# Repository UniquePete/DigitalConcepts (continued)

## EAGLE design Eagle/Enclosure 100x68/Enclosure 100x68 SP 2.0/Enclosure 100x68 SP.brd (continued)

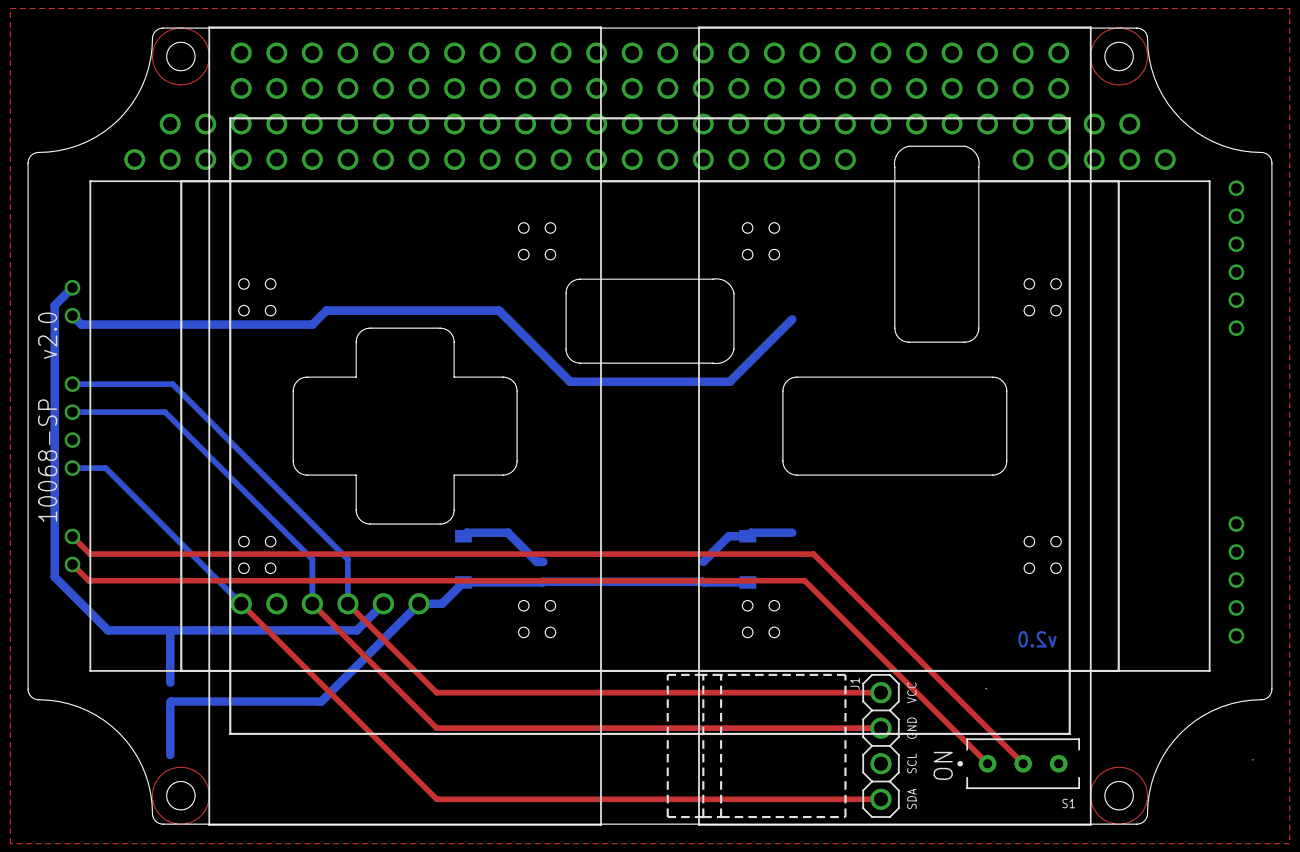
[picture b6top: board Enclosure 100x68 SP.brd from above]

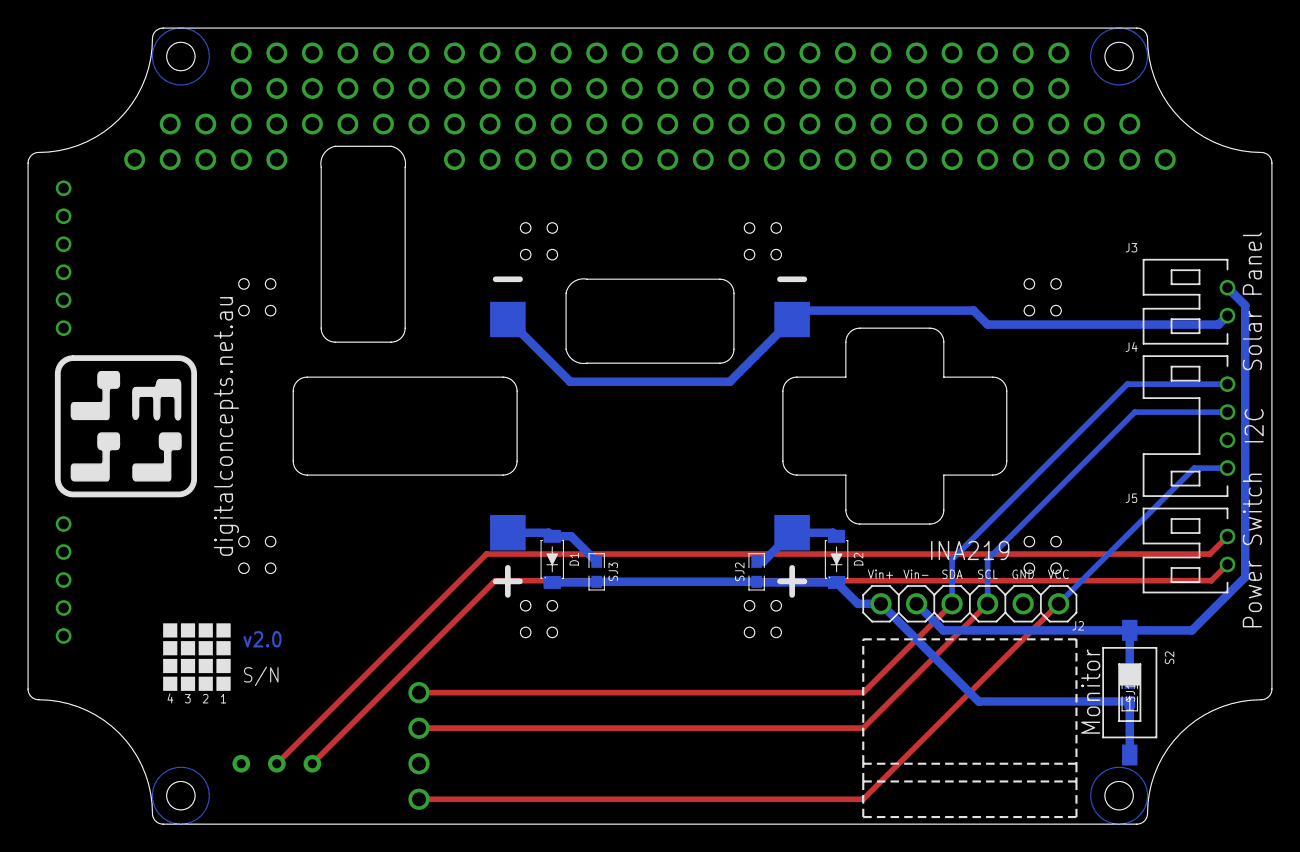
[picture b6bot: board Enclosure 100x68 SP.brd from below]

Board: 2 copper layers, 88.9 x 56.9 mm, 17 parts (14 on the bottom side), 11 nets.

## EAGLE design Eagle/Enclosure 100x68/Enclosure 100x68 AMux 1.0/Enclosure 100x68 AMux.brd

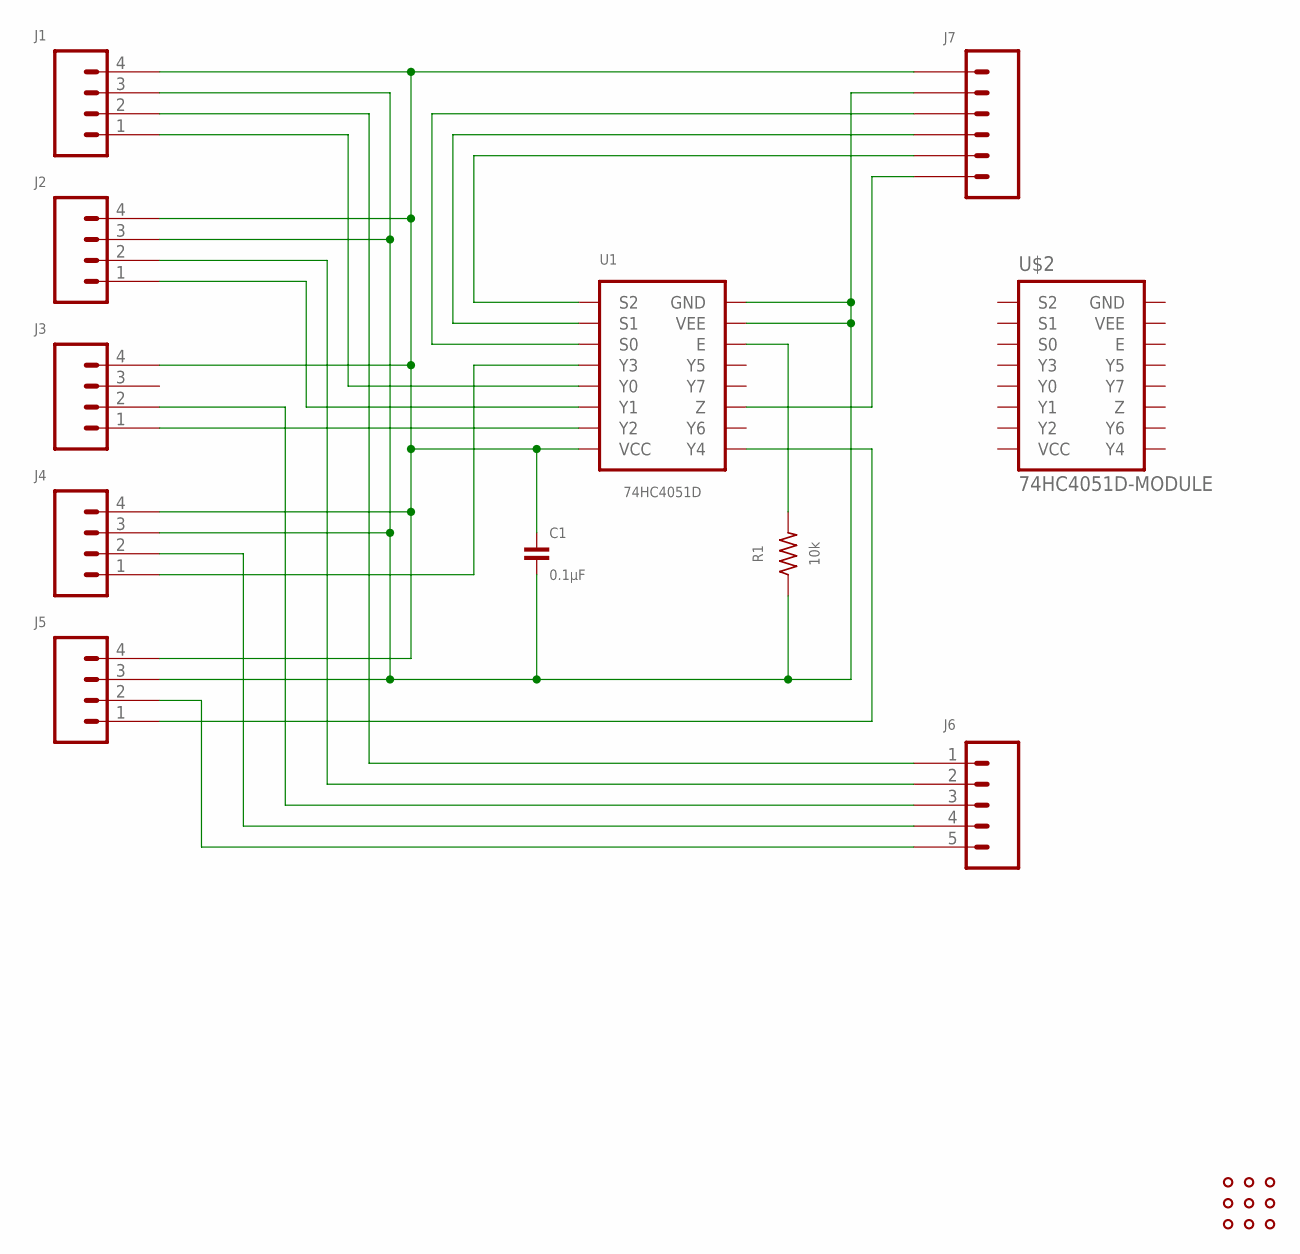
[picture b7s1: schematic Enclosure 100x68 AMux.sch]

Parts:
C1: 0.1µF; C0805
J1, J2, J3, J4, J5: HEADER-1X4-GENERIC; CONN_04-GENERIC
J6: JST-PH2.0-5-HORIZONTAL
J7: JST-PH2.0-6-HORIZONTAL
R1: 10k; R0805
U1: 74HC4051D; SOP16
U$1: PROTO-34X22-AMUX
U$2: 74HC4051D-MODULE

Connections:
GND: C1.2, J1.3, J2.3, J4.3, J5.3, J7.2, R1.1, U1.7 (VEE), U1.8 (GND)
unnamed: J4.1, U1.12 (Y3)
unnamed: J2.1, U1.14 (Y1)
unnamed: J1.1, U1.13 (Y0)
unnamed: J3.1, U1.15 (Y2)
unnamed: J5.1, U1.1 (Y4)
unnamed: J7.3, U1.11 (S0)
unnamed: J7.4, U1.10 (S1)
unnamed: R1.2, U1.6 (E)
unnamed: J7.6, U1.3 (Z)
unnamed: J1.2, J6.1
unnamed: J7.5, U1.9 (S2)
unnamed: J2.2, J6.2
unnamed: J3.2, J6.3
unnamed: J4.2, J6.4
unnamed: J5.2, J6.5
unnamed: C1.1, J1.4, J2.4, J3.4, J4.4, J5.4, J7.1, U1.16 (VCC)

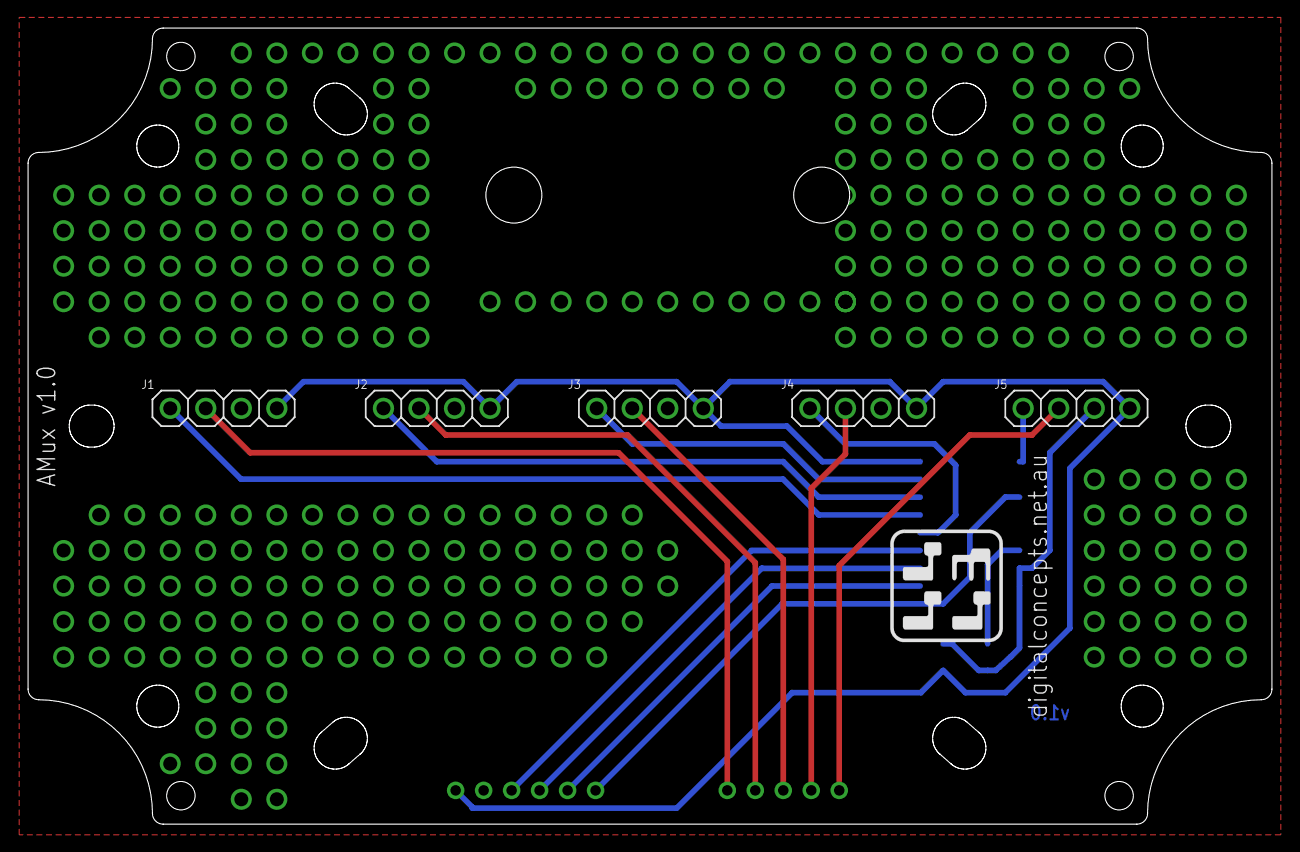
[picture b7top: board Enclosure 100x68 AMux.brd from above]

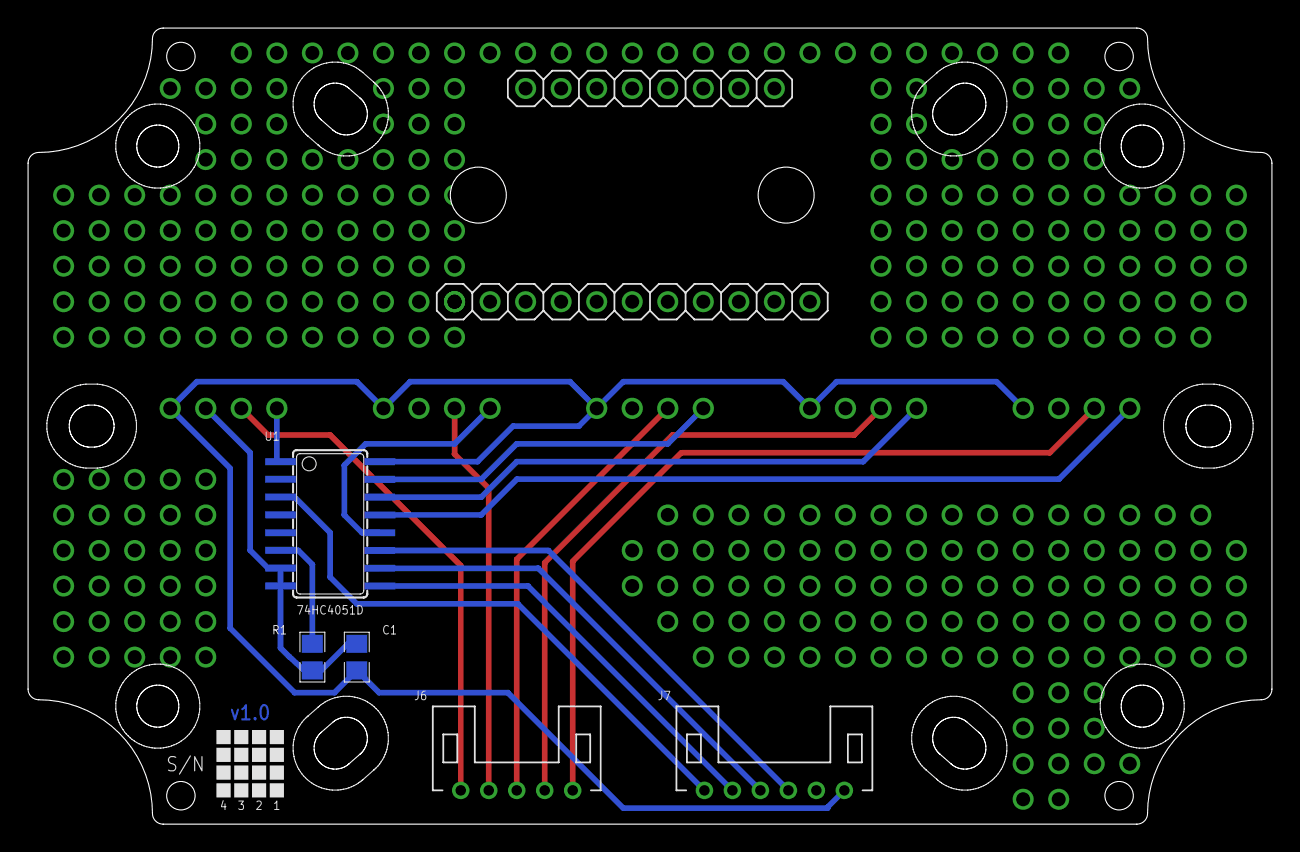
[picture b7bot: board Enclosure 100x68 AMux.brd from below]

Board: 2 copper layers, 88.9 x 56.9 mm, 12 parts (6 on the bottom side), 17 nets.

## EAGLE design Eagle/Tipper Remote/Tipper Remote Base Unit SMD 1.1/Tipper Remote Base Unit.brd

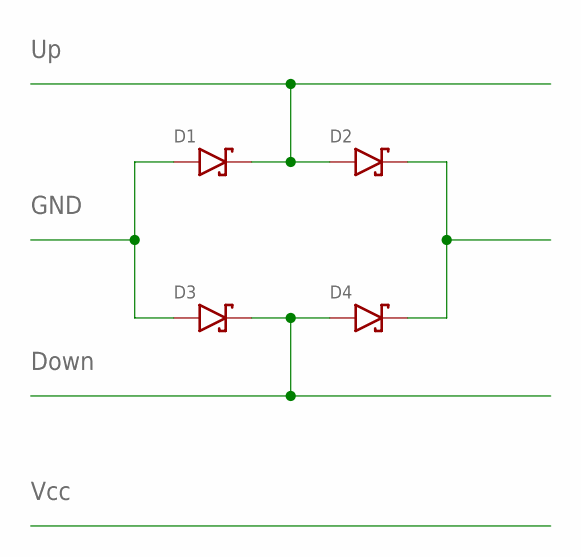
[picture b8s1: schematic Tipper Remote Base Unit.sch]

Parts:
D1, D2, D3, D4: DIODE-SCHOTTKY-1N5822; DIODE_SMB

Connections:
unnamed: D1.C, D2.A
unnamed: D3.C, D4.A
unnamed: D1.A, D3.A
unnamed: D2.C, D4.C

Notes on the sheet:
Down
GND
Vcc

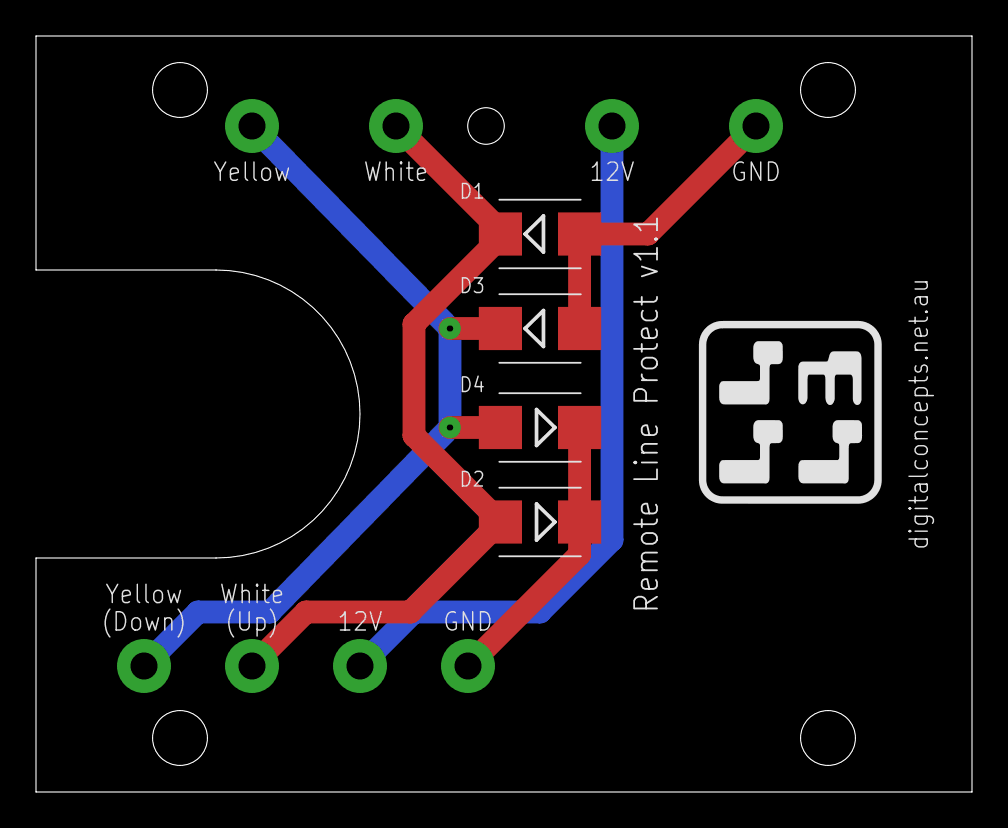
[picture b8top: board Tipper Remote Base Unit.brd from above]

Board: 2 copper layers, 52.0 x 42.0 mm, 4 parts (0 on the bottom side), 4 nets.

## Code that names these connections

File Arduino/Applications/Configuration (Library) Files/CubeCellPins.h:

// Heltec CubeCell Dev-Board pin identifiers

// CubeCell predefined pin names
/*
		ADC

		GPIO0
		GPIO1
		PWM1			// GPIO2
		GPIO2
		PWM2			// GPIO3
		GPIO3
		RGB				// GPIO4
		GPIO4
		GPIO5
		Vext			// GPIO6
		GPIO6
		VBAT_ADC_CTL	// GPIO7
		USER_KEY		// GPIO7
		GPIO7

		UART_TX
		UART_RX

		SCL
		SDA

		MISO
		MOSI
		SCK
		SS
*/

// I2C
// Nothing required here, SDA & SCL already defined

// ALF4all
#define A4a_A0				ADC
#define A4a_A1				GPIO5
#define A4a_A2				GPIO1
#define A4a_A3				GPIO0

// Wind/Rain>
#define rainCollectorPin	GPIO5
#define windDirectionPin	ADC
#define windSpeedPin		GPIO0

// Sensor Interface
#define sensorWake			GPIO2
#define sensorInterrupt		GPIO3

#define sphygOUT			GPIO2
#define sphygSCK			GPIO3

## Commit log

2025-05-01 Initial Upload
2025-05-01 Filename Update
2025-05-01 Add configuration files
2025-05-02 README Updates
    Update README.md file content
2025-05-09 New Part
    Add FP6277 and SX1308 Boost Converter Modules
2025-07-04 Arduino and Fritzing File Update
    Update EepromHandler
    Update PacketHandler
    Add new Utility Sketches
    Add new and update several Fritzing Parts
2025-09-01 SyntaxHighlighter
    Initial Commit
2025-09-01 2.2.0
    2.2.0 12 jun 2025
2025-09-01 2.2.1
    Modify numeric string match to exclude numerics preceded by "_"
2025-09-01 2.2.2
    Modify numeric string match to include qualifiers - preceding "-", decimal point in floating point numbers and suffix qualifiers (e.g. "f" for floating point numbers)
2025-09-01 2.2.3
    Add #if, #else & #elif to the ide-system-keyword list
2025-09-01 2.2.4
    Correct handling of block comments when included inline
2025-09-01 New and Updated Parts
    Several new and updated parts
2025-09-01 Initial Commit
    Initial commit
2025-09-06 Update README.md
    Add a bit more information about the current content.
2025-09-08 Correct handling of HTML tag attributes
